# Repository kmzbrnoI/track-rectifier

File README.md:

Model Track Rectifier
=====================

... to measure DCC voltage with multimeter.

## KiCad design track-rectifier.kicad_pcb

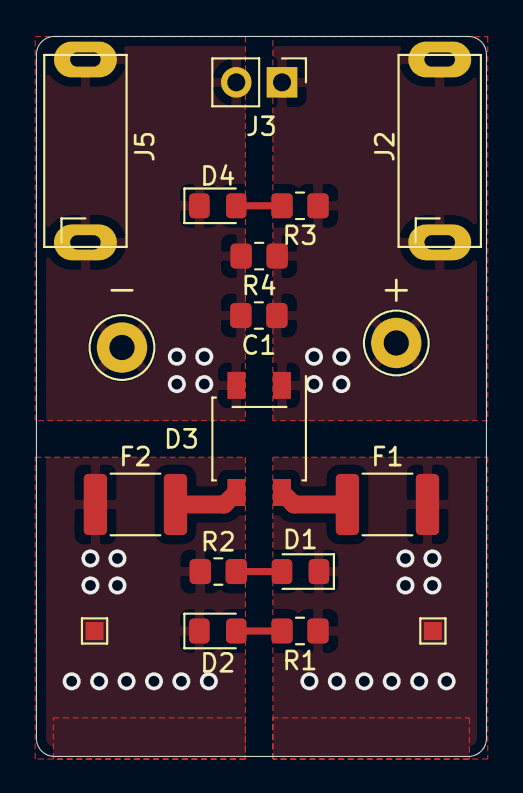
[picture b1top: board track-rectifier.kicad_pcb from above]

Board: 2 copper layers, 25.0 x 40.0 mm, 18 parts (0 on the bottom side), 9 nets.

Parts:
C1: 100n; R_0805_2012Metric_Pad1.20x1.40mm_HandSolder
D1, D2, D4: LED; LED_0805_2012Metric_Pad1.15x1.40mm_HandSolder
D3: S250
F1, F2: 500mA; Fuse_1812_4532Metric_Pad1.30x3.40mm_HandSolder
J1, J4: PAD; TestPoint_Pad_1.0x1.0mm
J2, J5: MPB1
J3: Screw_Terminal_01x02; PinHeader_1x02_P2.54mm_Vertical
R1, R2, R3: 1k; R_0805_2012Metric_Pad1.20x1.40mm_HandSolder
R4: R; R_0805_2012Metric_Pad1.20x1.40mm_HandSolder
TP1, TP2: TestPoint_Probe; TestPoint_Loop_D3.50mm_Drill1.4mm_Beaded

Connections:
/J: D1.1, F1.2, J1.1, R1.1
/K: D2.1, F2.1, J4.1, R2.1
GND: C1.2, D3.2, D4.1, J3.2, J5.1, R4.2, TP2.1
unnamed: D1.2, R2.2
unnamed: D2.2, R1.2
unnamed: D3.3, F2.2
unnamed: D3.4, F1.1
unnamed: D4.2, R3.2
VCC: C1.1, D3.1, J2.1, J3.1, R3.1, R4.1, TP1.1

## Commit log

2021-12-02 Add .gitignore, empty schematics & pcb.
2021-12-02 Draw schematics.
2021-12-07 Add rectifier footprint.
2021-12-07 Add MPB1 measure connector.
2021-12-07 Add PCB.
2021-12-09 Add silkscreen place for Vdrop.
2021-12-09 Make touch polygon wider.
2021-12-09 Change name to "Track Rectifier".
2021-12-09 Add README.
2021-12-09 Add JLCPCB fab makefile.
2021-12-16 Add PTC on inputs.
